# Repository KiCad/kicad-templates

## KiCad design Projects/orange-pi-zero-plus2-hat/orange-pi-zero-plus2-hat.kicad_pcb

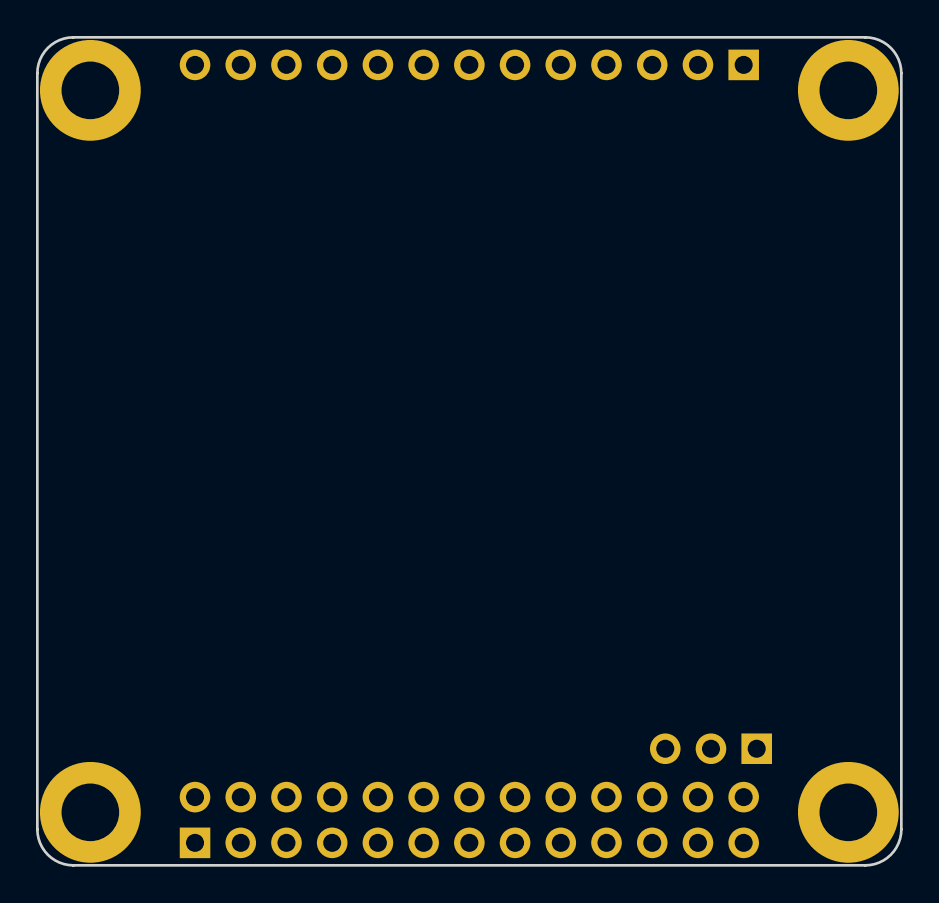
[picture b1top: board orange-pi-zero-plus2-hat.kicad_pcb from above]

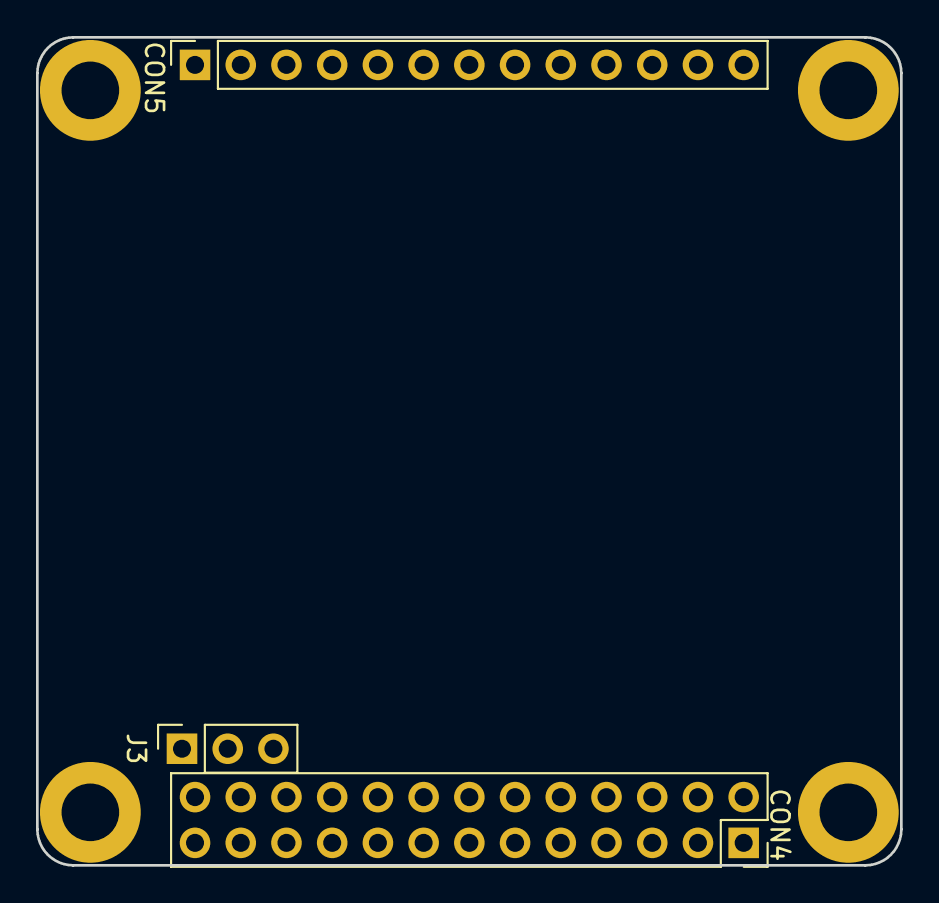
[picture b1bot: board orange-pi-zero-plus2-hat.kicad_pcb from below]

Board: 2 copper layers, 48.0 x 46.0 mm, 3 parts (3 on the bottom side), 3 nets, no tracks yet.

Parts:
CON4: Conn_02x13_Odd_Even; PinSocket_2x13_P2.54mm_Vertical
CON5: Conn_01x13; PinSocket_1x13_P2.54mm_Vertical
J3: Conn_01x03; PinSocket_1x03_P2.54mm_Vertical

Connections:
/3.3V: CON4.1, CON4.17
/5V: CON4.2, CON4.4, CON5.1
/GND: CON4.6, CON4.9, CON4.14, CON4.20, CON4.25, CON5.2, J3.1

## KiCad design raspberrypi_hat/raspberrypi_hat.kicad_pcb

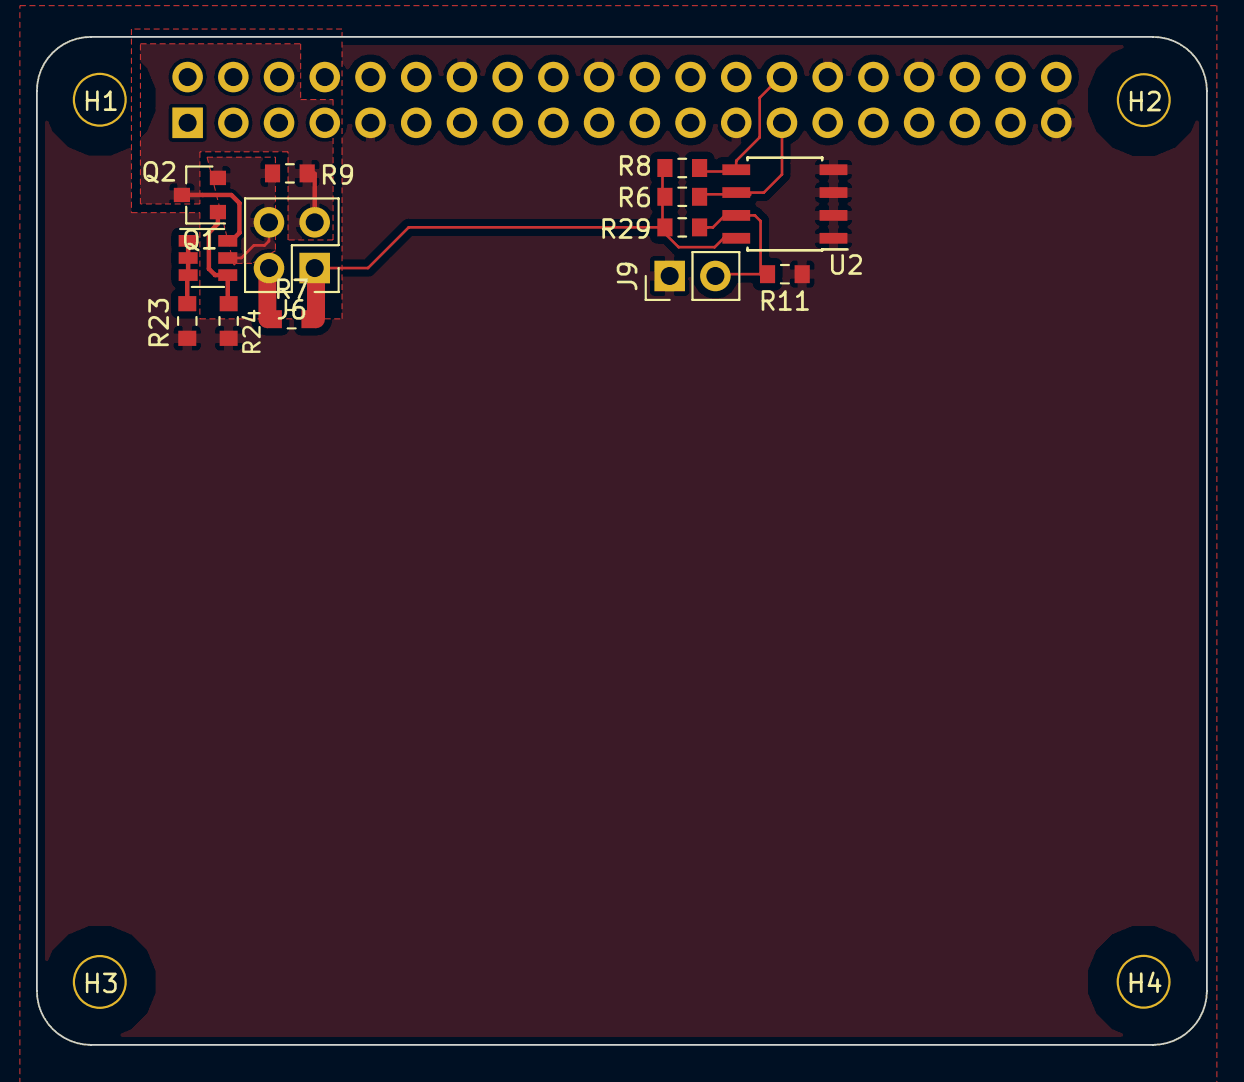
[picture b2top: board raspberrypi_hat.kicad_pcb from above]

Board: 4 copper layers, 65.0 x 56.0 mm, 18 parts (1 on the bottom side), 10 nets.

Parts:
H1, H2, H3, H4: 3mm_Mounting_Hole; NPTH_3mm_ID
J3: 40HAT; PinSocket_2x20_P2.54mm_Vertical
J6: CONN_02X02; PinHeader_2x02_P2.54mm_Vertical
J9: CONN_01X02; PinHeader_1x02_P2.54mm_Vertical
Q1: DMG2305UX; SOT-23
Q2: DMMT5401; SOT-23-6
R6, R8: 3.9K; R_0603_1608Metric_Pad0.84x1.00mm_HandSolder
R7, R9, R11: DNP; R_0603_1608Metric_Pad0.84x1.00mm_HandSolder
R23, R24: 22; R_0603_1608Metric_Pad0.84x1.00mm_HandSolder
R29: 10K; R_0603_1608Metric_Pad0.84x1.00mm_HandSolder
U2: CAT24C32; SOIC-8_3.9x4.9mm_P1.27mm

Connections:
/ID_SC_EEPROM: J3.28, R8.2, U2.5
/ID_SD_EEPROM: J3.27, R6.2, U2.6
/P3V3: J6.1, R6.1, R7.2, R8.1, R29.1, U2.8
/P3V3_HAT: J3.1, J6.2, R7.1
/P5V: J6.3, Q1.3, Q2.6, R9.2
/P5V_HAT: J3.2, J3.4, J6.4, Q1.2, Q2.5, R9.1
GND: J3.6, J3.9, J3.14, J3.20, J3.25, J3.30, J3.34, J3.39, J9.1, R11.2, R23.2, R24.2, U2.1, U2.2, U2.3, U2.4
unnamed: J9.2, R11.1, R29.2, U2.7
unnamed: Q1.1, Q2.4, R24.1
unnamed: Q2.1, Q2.2, Q2.3, R23.1
